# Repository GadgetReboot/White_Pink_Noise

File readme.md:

<BR><BR><BR>
White and Pink noise generating PCB<BR>
Uses a linear feedback shift register in an ATTiny85 to generate pseudo random white noise<BR>
Then uses a -3 dB/octave low pass RC filter to convert to pink noise.<BR>
ATTiny Sketch: https://github.com/GadgetReboot/White_Noise_LFSR

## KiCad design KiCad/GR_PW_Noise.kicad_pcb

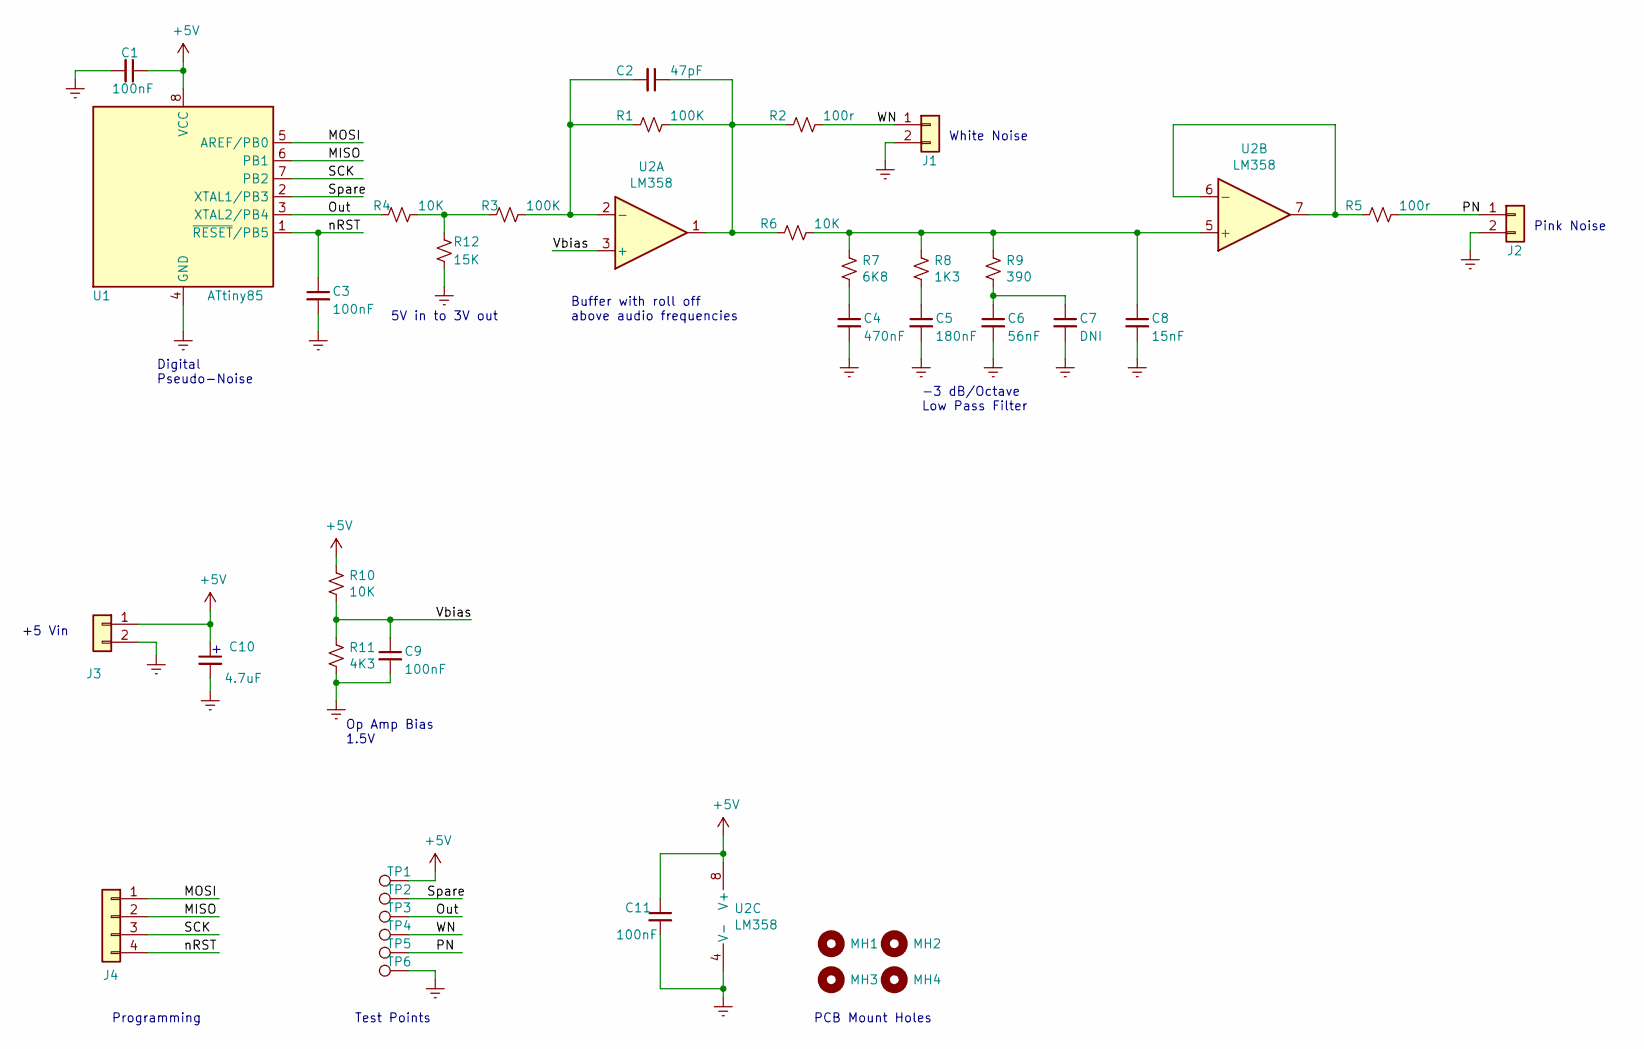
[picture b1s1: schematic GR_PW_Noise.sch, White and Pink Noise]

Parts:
C1, C3, C9, C11: 100nF; C_Disc_D3.8mm_W2.6mm_P2.50mm
C2: 47pF; C_Disc_D3.8mm_W2.6mm_P2.50mm
C4: 470nF; C_Disc_D3.8mm_W2.6mm_P2.50mm
C5: 180nF; C_Disc_D3.8mm_W2.6mm_P2.50mm
C6: 56nF; C_Disc_D3.8mm_W2.6mm_P2.50mm
C7: DNI; C_Disc_D3.8mm_W2.6mm_P2.50mm
C8: 15nF; C_Disc_D3.8mm_W2.6mm_P2.50mm
C10: 4.7uF; C_Disc_D3.8mm_W2.6mm_P2.50mm
J1, J2, J3: Conn_01x02; PinHeader_1x02_P2.54mm_Vertical
J4: Conn_01x04; PinHeader_1x04_P2.54mm_Vertical
MH1, MH2, MH3, MH4: MountingHole; MountingHole_3.2mm_M3
R1, R3: 100K; R_Axial_DIN0204_L3.6mm_D1.6mm_P7.62mm_Horizontal
R2, R5: 100r; R_Axial_DIN0204_L3.6mm_D1.6mm_P7.62mm_Horizontal
R4, R6, R10: 10K; R_Axial_DIN0204_L3.6mm_D1.6mm_P7.62mm_Horizontal
R7: 6K8; R_Axial_DIN0204_L3.6mm_D1.6mm_P7.62mm_Horizontal
R8: 1K3; R_Axial_DIN0204_L3.6mm_D1.6mm_P7.62mm_Horizontal
R9: 390; R_Axial_DIN0204_L3.6mm_D1.6mm_P7.62mm_Horizontal
R11: 4K3; R_Axial_DIN0204_L3.6mm_D1.6mm_P7.62mm_Horizontal
R12: 15K; R_Axial_DIN0204_L3.6mm_D1.6mm_P7.62mm_Horizontal
TP1, TP2, TP3, TP4, TP5, TP6: TestPoint; TestPoint_Pad_D1.5mm
U1: ATtiny85; DIP-8_W7.62mm
U2: LM358; DIP-8_W7.62mm

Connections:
+5V: C1.1, C10.1, C11.1, J3.1, R10.2, TP1.1, U1.8 (VCC), U2.8 (V+)
/MISO: J4.2, U1.6 (PB1)
/MOSI: J4.1, U1.5 (AREF/PB0)
/Out: R4.1, TP3.1, U1.3 (XTAL2/PB4)
/PN: J2.1, R5.2, TP5.1
/SCK: J4.3, U1.7 (PB2)
/Spare: TP2.1, U1.2 (XTAL1/PB3)
/Vbias: C9.1, R10.1, R11.2, U2.3 (+)
/WN: J1.1, R2.2, TP4.1
/nRST: C3.1, J4.4, U1.1 (~RESET~/PB5)
GNDREF: C1.2, C3.2, C4.2, C5.2, C6.2, C7.2, C8.2, C9.2, C10.2, C11.2, J1.2, J2.2, J3.2, R11.1, R12.2, TP6.1, U1.4 (GND), U2.4 (V-)
unnamed: C2.1, R1.2, R2.1, R6.1, U2.1
unnamed: C2.2, R1.1, R3.2, U2.2 (-)
unnamed: C4.1, R7.1
unnamed: C5.1, R8.1
unnamed: C6.1, C7.1, R9.1
unnamed: C8.1, R6.2, R7.2, R8.2, R9.2, U2.5 (+)
unnamed: R5.1, U2.6 (-), U2.7
unnamed: R3.1, R4.2, R12.1

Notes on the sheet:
+5 Vin
PCB Mount Holes
Pink Noise
White Noise
-3 dB/Octave Low Pass Filter
Digital Pseudo-Noise
Test Points
Programming
Op Amp Bias 1.5V
5V in to 3V out
Buffer with roll off above audio frequencies

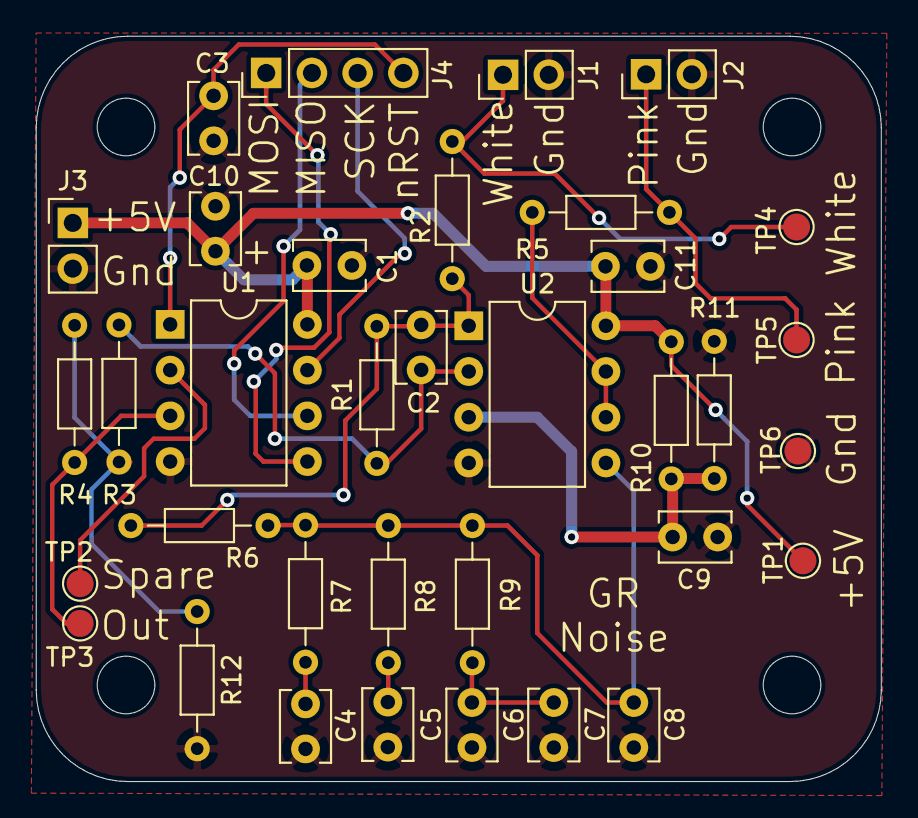
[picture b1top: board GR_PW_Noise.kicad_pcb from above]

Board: 2 copper layers, 46.9 x 41.4 mm, 39 parts (0 on the bottom side), 19 nets.
